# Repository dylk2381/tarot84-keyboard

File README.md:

# tarot84-keyboard
An 84-key 65%+numpad keyboard. Name is just something I decided like 95% of the way through :P.

## A note
I am actually unsure if this works properly at the moment. I am planning on ordering some prototype PCBs whenever some of the components come back in stock. As of now, this is just a fun side project that I decided to throw up on github. This is my first time designing *any* PCB.

## Specifications
 - 84 keys
 - Alpha, Numbers, Numpad, Nav keys
 - Supports MX-Style switches (3pin or 5pin)
 - Supports QMK (Not sure about any alternatives, should be anything compatible with the ATMEGA32U4-A)
 - Soldered

## Component List
NOTE: All of the components on this list are just what I have found, they should work with anything that is equivalent.
 - 1x ATMEGA32U4-A TQFB Package Microcontroller
 - 84x YFW 1N4148WS Diodes
 - 2x CL21C220JBANNNC Capacitors
 - 2x 0805W8F220JT5E Resistors
 - 3x C0805C104K3REC7800 Capacitors
 - 1x 0805B105K250NT Capacitor
 - 1x 0805X106K250NT Capacitor
 - 2x 0805W8F1002T5E Resistors
 - 1x X322516MLB4SI Crystal
 - 1x RS-187R05A2-DS MT RT Switch
 - 1x SM04B-SRSS-TB(LF)(SN) 4 Pin Connector

## Required Libraries
https://github.com/ai03-2725/MX_Alps_Hybrid
https://github.com/egladman/keebs.pretty
https://github.com/tmk/keyboard_parts.pretty
https://github.com/ai03-2725/Unified-Daughterboard
https://github.com/ai03-2725/random-keyboard-parts.pretty
https://github.com/tmk/kicad_lib_tmk

## Assembly
I believe everything on this board *should* be able to be hand soldered, albeit designed with just ordering assembly online in mind. If you are assembling, I would strongly recommend not relying entirely on the silkscreening.

## Additional Info
Screenshots are in the folder labelled "Screenshots."

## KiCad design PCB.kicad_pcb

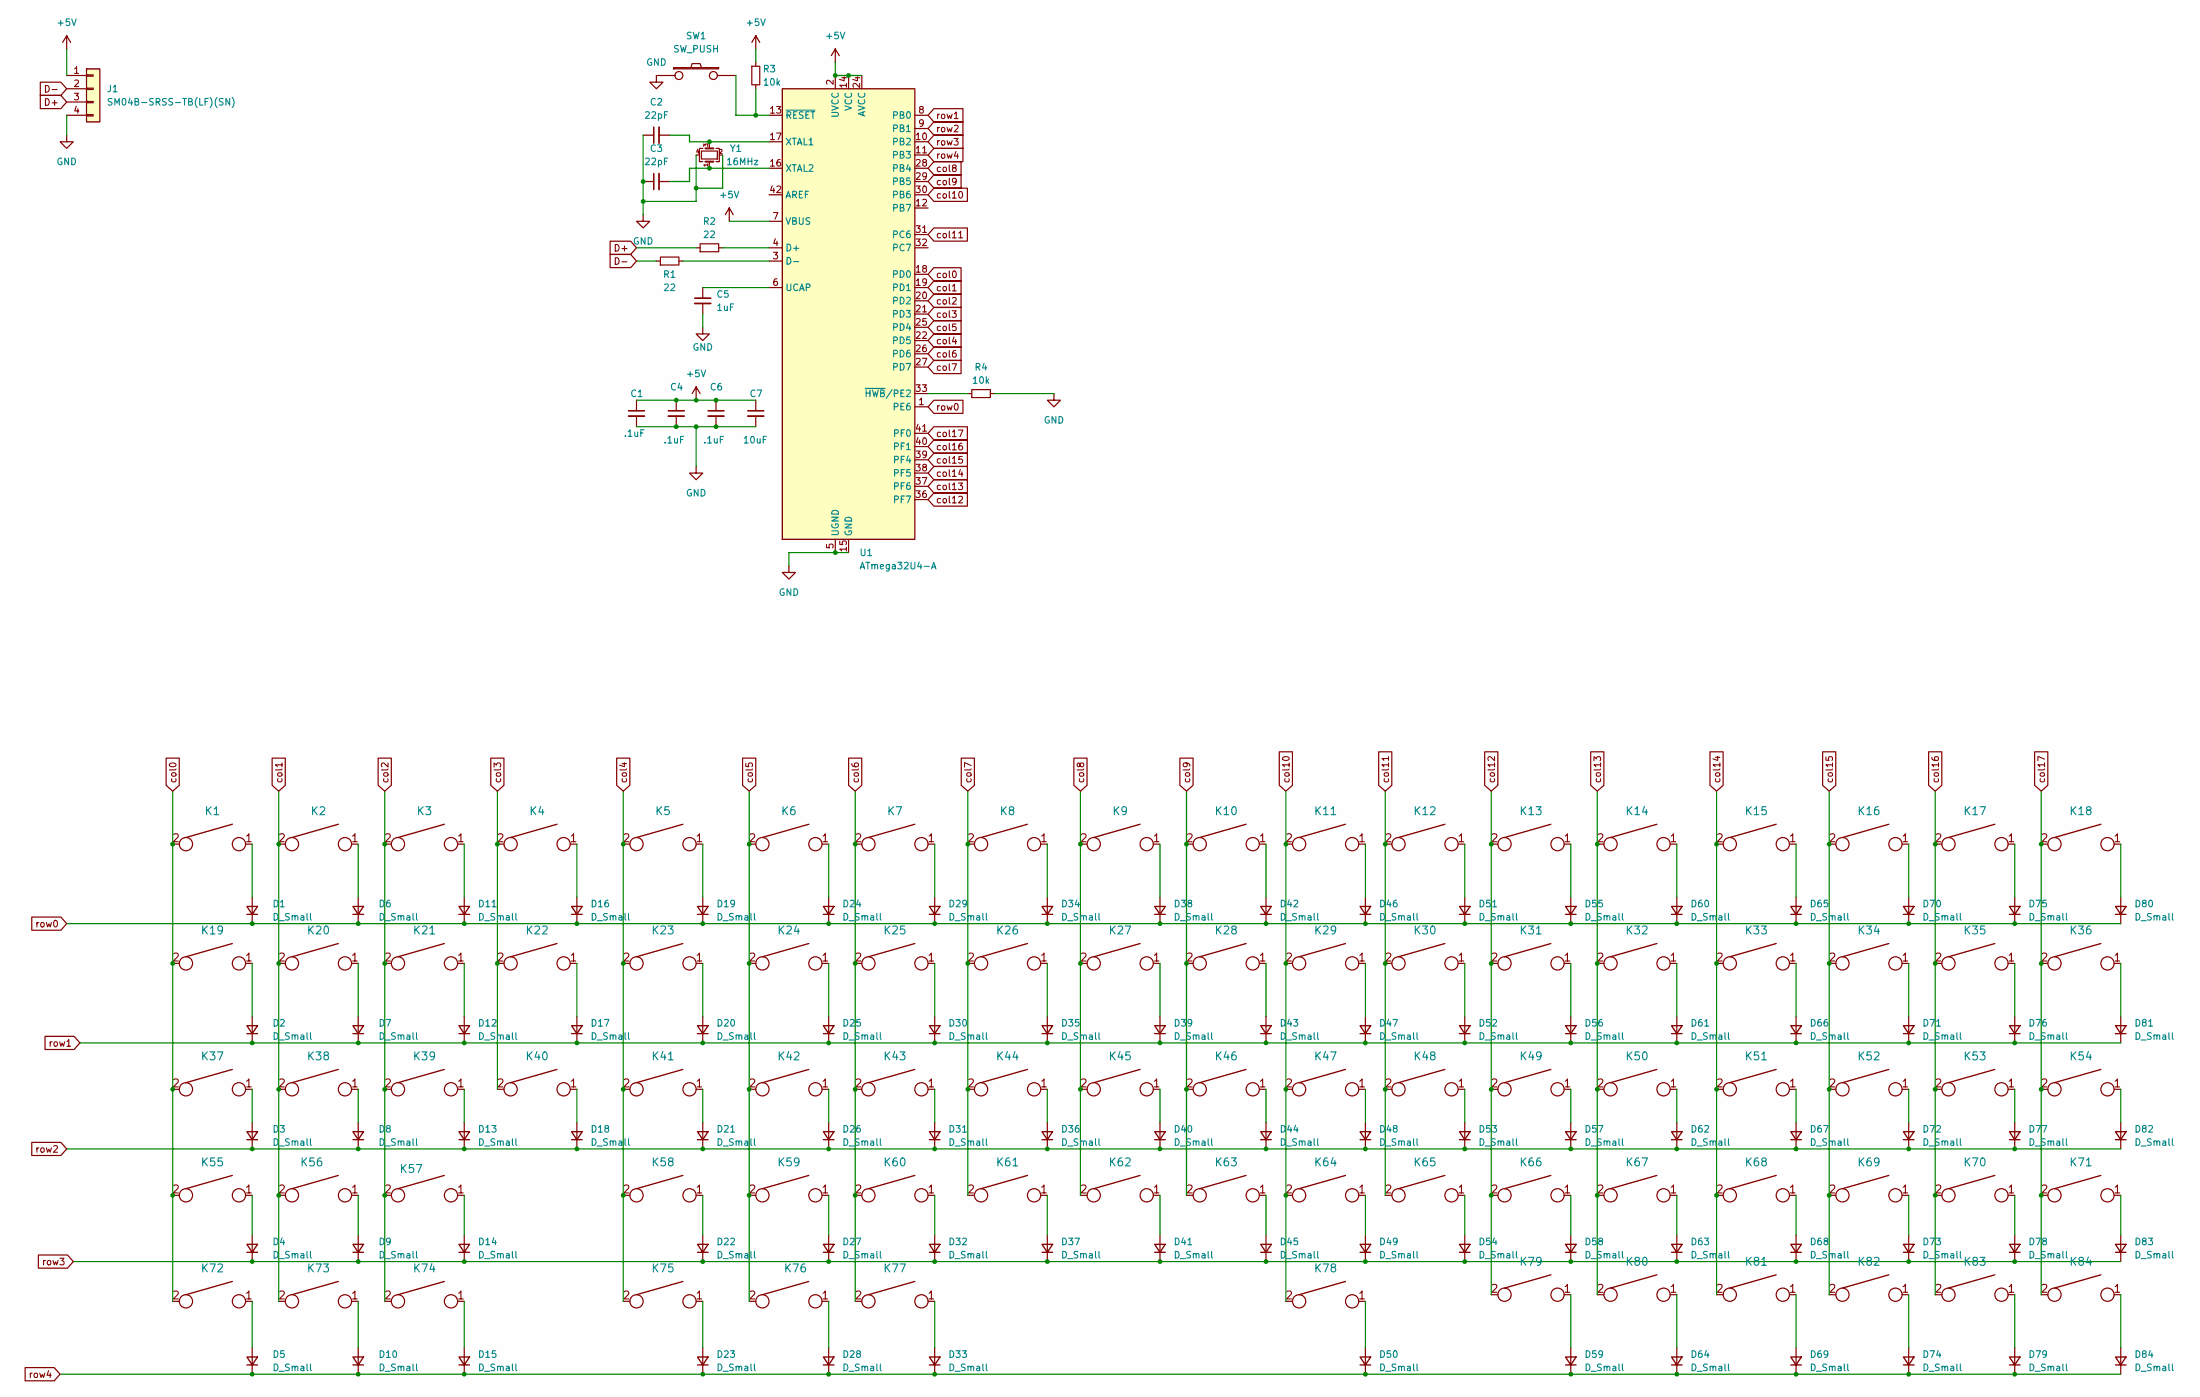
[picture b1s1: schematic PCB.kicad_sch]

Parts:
C1, C4, C6: .1uF; C_0805_2012Metric_Pad1.18x1.45mm_HandSolder
C2, C3: 22pF; C_0805_2012Metric_Pad1.18x1.45mm_HandSolder
C5: 1uF; C_0805_2012Metric_Pad1.18x1.45mm_HandSolder
C7: 10uF; C_0805_2012Metric_Pad1.18x1.45mm_HandSolder
D1, D2, D3, D4, D5, D6, D7, D8, D9, D10, D11, D12, D13, D14, D15, D16, D17, D18, D19, D20, D21, D22, D23, D24, D25, D26, D27, D28, D29, D30, D31, D32, D33, D34, D35, D36, D37, D38, D39, D40, D41, D42, D43, D44, D45, D46, D47, D48, D49, D50, D51, D52, D53, D54, D55, D56, D57, D58, D59, D60, D61, D62, D63, D64, D65, D66, D67, D68, D69, D70, D71, D72, D73, D74, D75, D76, D77, D78, D79, D80, D81, D82, D83, D84: D_Small; D_SOD-123
J1: SM04B-SRSS-TB(LF)(SN); JST-SR-4
K1, K2, K3, K4, K5, K6, K7, K8, K9, K10, K11, K12, K13, K14, K15, K16, K17, K18, K19, K20, K21, K22, K23, K24, K25, K26, K27, K28, K29, K30, K31, K32, K33, K34, K35, K36, K37, K38, K39, K40, K41, K42, K43, K44, K45, K46, K47, K48, K49, K50, K51, K52, K53, K54, K55, K56, K57, K58, K59, K60, K61, K62, K63, K64, K65, K66, K67, K68, K69, K70, K71, K72, K73, K74, K75, K76, K77, K78, K79, K80, K81, K82, K83, K84: KEYSW; MXOnly-1U-NoLED
R1, R2: 22; R_0805_2012Metric
R3, R4: 10k; R_0805_2012Metric
SW1: SW_PUSH; SKQG-1155865
U1: ATmega32U4-A; TQFP-44_10x10mm_P0.8mm
Y1: 16MHz; Crystal_SMD_3225-4Pin_3.2x2.5mm

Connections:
+5V: C1.1, C4.1, C6.1, C7.1, J1.1, R3.1, U1.2 (UVCC), U1.7 (VBUS), U1.14 (VCC), U1.24 (AVCC), U1.34 (VCC), U1.44 (AVCC)
D+: J1.3, R2.1
D-: J1.2, R1.1
GND: C1.2, C2.1, C3.1, C4.2, C5.2, C6.2, C7.2, J1.4, R4.2, SW1.1, U1.5 (UGND), U1.15 (GND), U1.23 (GND), U1.35 (GND), U1.43 (GND), Y1.2, Y1.4
unnamed: C2.2, U1.17 (XTAL1), Y1.3
unnamed: C3.2, U1.16 (XTAL2), Y1.1
unnamed: C5.1, U1.6 (UCAP)
unnamed: D1.2 (A), K1.1
unnamed: D2.2 (A), K19.1
unnamed: D3.2 (A), K37.1
unnamed: D4.2 (A), K55.1
unnamed: D5.2 (A), K72.1
unnamed: D6.2 (A), K2.1
unnamed: D7.2 (A), K20.1
unnamed: D8.2 (A), K38.1
unnamed: D9.2 (A), K56.1
unnamed: D10.2 (A), K73.1
unnamed: D11.2 (A), K3.1
unnamed: D12.2 (A), K21.1
unnamed: D13.2 (A), K39.1
unnamed: D14.2 (A), K57.1
unnamed: D15.2 (A), K74.1
unnamed: D16.2 (A), K4.1
unnamed: D17.2 (A), K22.1
unnamed: D18.2 (A), K40.1
unnamed: D19.2 (A), K5.1
unnamed: D20.2 (A), K23.1
unnamed: D21.2 (A), K41.1
unnamed: D22.2 (A), K58.1
unnamed: D23.2 (A), K75.1
unnamed: D24.2 (A), K6.1
unnamed: D25.2 (A), K24.1
unnamed: D26.2 (A), K42.1
unnamed: D27.2 (A), K59.1
unnamed: D28.2 (A), K76.1
unnamed: D29.2 (A), K7.1
unnamed: D30.2 (A), K25.1
unnamed: D31.2 (A), K43.1
unnamed: D32.2 (A), K60.1
unnamed: D33.2 (A), K77.1
unnamed: D34.2 (A), K8.1
unnamed: D35.2 (A), K26.1
unnamed: D36.2 (A), K44.1
unnamed: D37.2 (A), K61.1
unnamed: D38.2 (A), K9.1
unnamed: D39.2 (A), K27.1
unnamed: D40.2 (A), K45.1
unnamed: D41.2 (A), K62.1
unnamed: D42.2 (A), K10.1
unnamed: D43.2 (A), K28.1
unnamed: D44.2 (A), K46.1
unnamed: D45.2 (A), K63.1
unnamed: D46.2 (A), K11.1
unnamed: D47.2 (A), K29.1
unnamed: D48.2 (A), K47.1
unnamed: D49.2 (A), K64.1
unnamed: D50.2 (A), K78.1
unnamed: D51.2 (A), K12.1
unnamed: D52.2 (A), K30.1
unnamed: D53.2 (A), K48.1
unnamed: D54.2 (A), K65.1
unnamed: D55.2 (A), K13.1
unnamed: D56.2 (A), K31.1
unnamed: D57.2 (A), K49.1
unnamed: D58.2 (A), K66.1
unnamed: D59.2 (A), K79.1
unnamed: D60.2 (A), K14.1
unnamed: D61.2 (A), K32.1
unnamed: D62.2 (A), K50.1
unnamed: D63.2 (A), K67.1
unnamed: D64.2 (A), K80.1
unnamed: D65.2 (A), K15.1
unnamed: D66.2 (A), K33.1
unnamed: D67.2 (A), K51.1
unnamed: D68.2 (A), K68.1
unnamed: D69.2 (A), K81.1
unnamed: D70.2 (A), K16.1
unnamed: D71.2 (A), K34.1
unnamed: D72.2 (A), K52.1
unnamed: D73.2 (A), K69.1
unnamed: D74.2 (A), K82.1
unnamed: D75.2 (A), K17.1
unnamed: D76.2 (A), K35.1
unnamed: D77.2 (A), K53.1
unnamed: D78.2 (A), K70.1
unnamed: D79.2 (A), K83.1
unnamed: D80.2 (A), K18.1
unnamed: D81.2 (A), K36.1
unnamed: D82.2 (A), K54.1
unnamed: D83.2 (A), K71.1
unnamed: D84.2 (A), K84.1
unnamed: R1.2, U1.3 (D-)
unnamed: R2.2, U1.4 (D+)
unnamed: R3.2, SW1.2, U1.13 (~RESET)
unnamed: R4.1, U1.33 (~HWB/PE2)
col0: K1.2, K19.2, K37.2, K55.2, K72.2, U1.18 (PD0)
col1: K2.2, K20.2, K38.2, K56.2, K73.2, U1.19 (PD1)
col2: K3.2, K21.2, K39.2, K57.2, K74.2, U1.20 (PD2)
col3: K4.2, K22.2, K40.2, U1.21 (PD3)
col4: K5.2, K23.2, K41.2, K58.2, K75.2, U1.22 (PD5)
col5: K6.2, K24.2, K42.2, K59.2, K76.2, U1.25 (PD4)
col6: K7.2, K25.2, K43.2, K60.2, K77.2, U1.26 (PD6)
col7: K8.2, K26.2, K44.2, K61.2, U1.27 (PD7)
col8: K9.2, K27.2, K45.2, K62.2, U1.28 (PB4)
col9: K10.2, K28.2, K46.2, K63.2, U1.29 (PB5)
col10: K11.2, K29.2, K47.2, K64.2, K78.2, U1.30 (PB6)
col11: K12.2, K30.2, K48.2, K65.2, U1.31 (PC6)
col12: K13.2, K31.2, K49.2, K66.2, K79.2, U1.36 (PF7)
col13: K14.2, K32.2, K50.2, K67.2, K80.2, U1.37 (PF6)
col14: K15.2, K33.2, K51.2, K68.2, K81.2, U1.38 (PF5)
col15: K16.2, K34.2, K52.2, K69.2, K82.2, U1.39 (PF4)
col16: K17.2, K35.2, K53.2, K70.2, K83.2, U1.40 (PF1)
col17: K18.2, K36.2, K54.2, K71.2, K84.2, U1.41 (PF0)
row0: D1.1 (K), D6.1 (K), D11.1 (K), D16.1 (K), D19.1 (K), D24.1 (K), D29.1 (K), D34.1 (K), D38.1 (K), D42.1 (K), D46.1 (K), D51.1 (K), D55.1 (K), D60.1 (K), D65.1 (K), D70.1 (K), D75.1 (K), D80.1 (K), U1.1 (PE6)
row1: D2.1 (K), D7.1 (K), D12.1 (K), D17.1 (K), D20.1 (K), D25.1 (K), D30.1 (K), D35.1 (K), D39.1 (K), D43.1 (K), D47.1 (K), D52.1 (K), D56.1 (K), D61.1 (K), D66.1 (K), D71.1 (K), D76.1 (K), D81.1 (K), U1.8 (PB0)
row2: D3.1 (K), D8.1 (K), D13.1 (K), D18.1 (K), D21.1 (K), D26.1 (K), D31.1 (K), D36.1 (K), D40.1 (K), D44.1 (K), D48.1 (K), D53.1 (K), D57.1 (K), D62.1 (K), D67.1 (K), D72.1 (K), D77.1 (K), D82.1 (K), U1.9 (PB1)
row3: D4.1 (K), D9.1 (K), D14.1 (K), D22.1 (K), D27.1 (K), D32.1 (K), D37.1 (K), D41.1 (K), D45.1 (K), D49.1 (K), D54.1 (K), D58.1 (K), D63.1 (K), D68.1 (K), D73.1 (K), D78.1 (K), D83.1 (K), U1.10 (PB2)
row4: D5.1 (K), D10.1 (K), D15.1 (K), D23.1 (K), D28.1 (K), D33.1 (K), D50.1 (K), D59.1 (K), D64.1 (K), D69.1 (K), D74.1 (K), D79.1 (K), D84.1 (K), U1.11 (PB3)

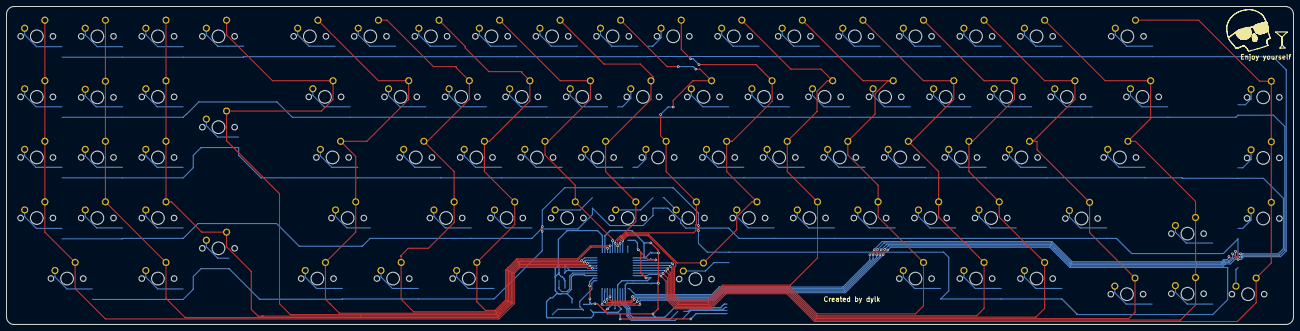
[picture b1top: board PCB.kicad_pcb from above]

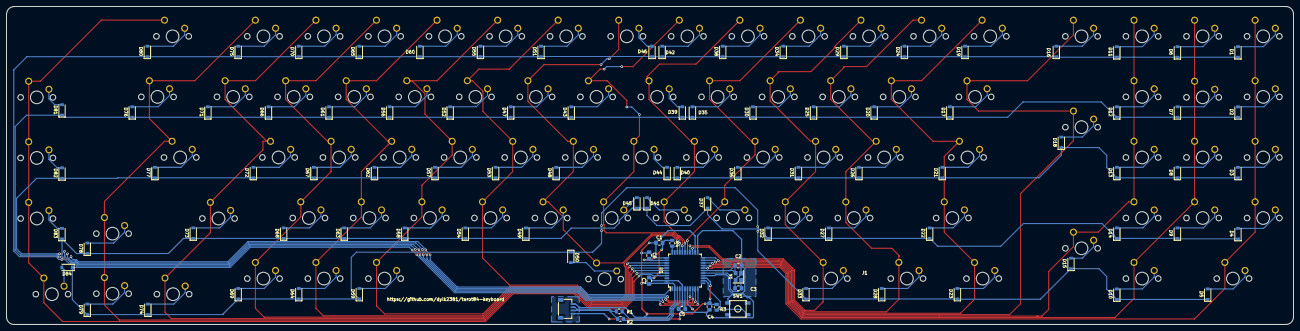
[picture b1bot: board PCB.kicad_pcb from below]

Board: 2 copper layers, 404.8 x 100.0 mm, 183 parts (99 on the bottom side), 118 nets.

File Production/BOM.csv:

Comment,Designator,Footprint,LCSC
".1uF","C1,C4,C6","Capacitor_SMD:C_0805_2012Metric_Pad1.18x1.45mm_HandSolder",""
"22pF","C2,C3","Capacitor_SMD:C_0805_2012Metric_Pad1.18x1.45mm_HandSolder",""
"1uF","C5","Capacitor_SMD:C_0805_2012Metric_Pad1.18x1.45mm_HandSolder",""
"10uF","C7","Capacitor_SMD:C_0805_2012Metric_Pad1.18x1.45mm_HandSolder",""
"D_Small","D1,D2,D3,D4,D5,D6,D7,D8,D9,D10,D11,D12,D13,D14,D15,D16,D17,D18,D19,D20,D21,D22,D23,D24,D25,D26,D27,D28,D29,D30,D31,D32,D33,D34,D35,D36,D37,D38,D39,D40,D41,D42,D43,D44,D45,D46,D47,D48,D49,D50,D51,D52,D53,D54,D55,D56,D57,D58,D59,D60,D61,D62,D63,D64,D65,D66,D67,D68,D69,D70,D71,D72,D73,D74,D75,D76,D77,D78,D79,D80,D81,D82,D83,D84","Diode_SMD:D_SOD-123",""
"SM04B-SRSS-TB(LF)(SN)","J1","random-keyboard-parts:JST-SR-4",""
"KEYSW","K1,K2,K3,K4,K5,K6,K7,K8,K9,K10,K11,K12,K13,K14,K15,K16,K17,K18,K19,K20,K21,K22,K23,K24,K25,K26,K27,K28,K29,K30,K31,K32,K33,K34,K35,K36,K37,K38,K39,K40,K41,K42,K43,K44,K45,K46,K47,K48,K49,K50,K51,K52,K53,K54,K55,K56,K57,K58,K59,K60,K61,K62,K63,K64,K65,K66,K67,K68,K69,K70,K71,K72,K73,K74,K75,K76,K77,K78,K79,K80,K81,K82,K83,K84","MX_Only:MXOnly-1U-NoLED",""
"22","R1,R2","Resistor_SMD:R_0805_2012Metric",""
"10k","R3,R4","Resistor_SMD:R_0805_2012Metric",""
"SW_PUSH","SW1","random-keyboard-parts:SKQG-1155865",""
"ATmega32U4-A","U1","Package_QFP:TQFP-44_10x10mm_P0.8mm",""
"16MHz","Y1","Crystal:Crystal_SMD_3225-4Pin_3.2x2.5mm",""
